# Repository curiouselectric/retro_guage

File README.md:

# retro_guage
A serial interfaced retro style guage for displaying info

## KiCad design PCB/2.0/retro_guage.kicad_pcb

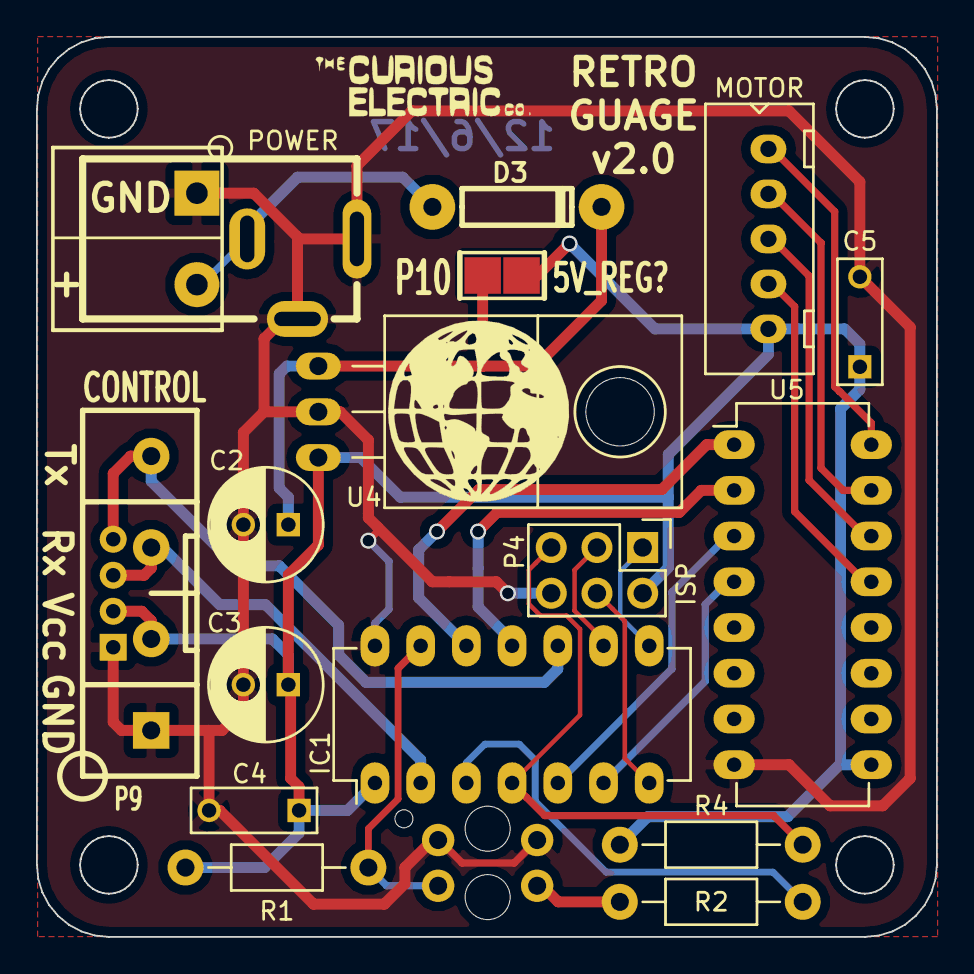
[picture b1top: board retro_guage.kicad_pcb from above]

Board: 2 copper layers, 50.0 x 50.0 mm, 20 parts (1 on the bottom side), 21 nets.

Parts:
C2, C3: 220u; C_Radial_D6.3_L11.2_P2.5
C4, C5: 100n; C_Rect_L7_W2.5_P5
CON1: POWER; DC_Power_2_1
D3: 1N400x; TH_Diode_1
IC1: ATTINY84A-PU; DIP-14_W7.62mm_LongPads
P2: POWER; TH_CONN_2W
P3: MOTOR; XHP-5
P4: ISP; Pin_Header_Straight_2x03
P6: LOGO1; CuriousElectric_flat_12mm
P8: LOGO2; CuriousElectric_globe_10mm
P9: CONTROL; SIL-4_Grove_SCREW
P10: 5V_REG?; SM_2_SLDR_JMP
R1, R4: 10K; Resistor_Horizontal_RM10mm
R2: 330R; Resistor_Horizontal_RM10mm
U3: TCRT5000
U4: 7805; TO-220_Neutral123_Horizontal
U5: ULN2003; DIP-16_W7.62mm_LongPads

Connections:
/IN1: IC1.12, U5.1
/IN2: IC1.11, U5.2
/IN3: IC1.5, U5.3
/IN4: IC1.6, U5.4
/MISO: IC1.8, P4.1
/MOSI: IC1.7, P4.4
/MOTOR_HOME_OUT: IC1.3, R2.1
/MOTOR_HOME_SENSE: IC1.13, R1.1, U3.1
/RST: IC1.4, P4.5, R4.1
/Rx: IC1.2, P9.3
/SCK: IC1.9, P4.3
/Tx: IC1.10, P9.4
GND: C2.2, C3.2, C4.2, C5.2, CON1.2, CON1.3, IC1.14, P2.1, P4.6, P9.1, U3.2, U3.3, U4.2, U5.8
unnamed: C2.1, D3.1, P10.1, U4.1
unnamed: CON1.1, D3.2, P2.2
unnamed: P3.1, U5.16
unnamed: P3.2, U5.15
unnamed: P3.3, U5.14
unnamed: P3.4, U5.13
unnamed: R2.2, U3.4
VCC: C3.1, C4.1, C5.1, IC1.1, P3.5, P4.2, P9.2, P10.2, R1.2, R4.2, U4.3, U5.9

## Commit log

2017-06-12 First commit of original PCB
2017-06-12 Update PCB - Guage only
